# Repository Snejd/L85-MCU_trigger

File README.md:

# ARMY L85 airsoft electric gun electronic trigger
The L85 from G&G (and it's copy ARMY) has some fundamental design flaws concerning trigger assembly and firing cycle principle. \
This project aims to improve on those by introducing MCU control based on two microtriggers sensing weapon trigger push and cycle of gun finished. \
Main concern for this project was make a very cheap solution compared to usual microcontroller driven firing mechanisms.

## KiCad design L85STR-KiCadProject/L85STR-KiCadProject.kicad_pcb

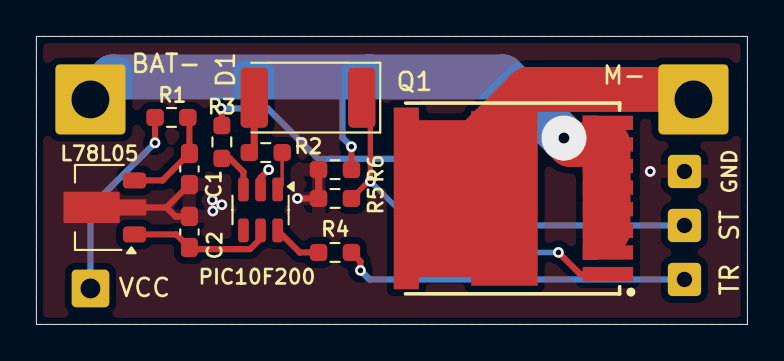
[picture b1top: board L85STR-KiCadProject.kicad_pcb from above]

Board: 2 copper layers, 39.5 x 16.0 mm, 18 parts (0 on the bottom side), 13 nets.

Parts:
BAT-: Conn_01x01_Socket; SolderWire-1.5sqmm_1x01_D1.7mm_OD3.9mm
C1: 0.33u; C_0603_1608Metric_Pad1.08x0.95mm_HandSolder
C2: 0.1u; C_0603_1608Metric_Pad1.08x0.95mm_HandSolder
D1: D; D_2512_6332Metric_Pad1.52x3.35mm_HandSolder
GND: Conn_01x01_Socket; SolderWire-0.25sqmm_1x01_D0.65mm_OD1.7mm
M-: Conn_01x01_Socket; SolderWire-1.5sqmm_1x01_D1.7mm_OD3.9mm
PIC10F200: PIC10F200-IMC; SOT-23-6
Q1: IPT004N03L; INF-PG-HSOF-8-1-0
R1, R2, R3, R4: 470R; R_0603_1608Metric_Pad0.98x0.95mm_HandSolder
R5: 1k; R_0603_1608Metric_Pad0.98x0.95mm_HandSolder
R6: 1M; R_0603_1608Metric_Pad0.98x0.95mm_HandSolder
ST: Conn_01x01_Socket; SolderWire-0.25sqmm_1x01_D0.65mm_OD1.7mm
TR: Conn_01x01_Socket; SolderWire-0.25sqmm_1x01_D0.65mm_OD1.7mm
U2: L78L05; SOT-89-3
VCC: Conn_01x01_Socket; SolderWire-0.5sqmm_1x01_D0.9mm_OD2.1mm

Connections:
GND: C1.2, C2.1, GND.1 (Pin_1_1), PIC10F200.2 (VSS), R5.1, R6.1, U2.2 (GND)
unnamed: D1.2 (A), R2.2
unnamed: D1.1 (K), Q1.1 (GATE), R5.2
unnamed: M-.1 (Pin_1_1), Q1.9 (DRAIN)
unnamed: BAT-.1 (Pin_1_1), Q1.2 (SOURCE), Q1.3 (SOURCE), Q1.4 (SOURCE), Q1.5 (SOURCE), Q1.6 (SOURCE), Q1.7 (SOURCE), Q1.8 (SOURCE), R6.2
unnamed: R4.1, TR.1 (Pin_1_1)
unnamed: R3.2, ST.1 (Pin_1_1)
unnamed: R1.1, VCC.1 (Pin_1_1)
unnamed: PIC10F200.1 (GP0), R2.1
unnamed: PIC10F200.3 (GP1), R3.1
unnamed: PIC10F200.6 (GP3), R4.2
unnamed: C2.2, PIC10F200.5 (VDD), U2.1 (OUT)
unnamed: C1.1, R1.2, U2.3 (IN)

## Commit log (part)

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2025-03-11 Init repo
    Already V1 of PCB finished
2025-03-11 License
